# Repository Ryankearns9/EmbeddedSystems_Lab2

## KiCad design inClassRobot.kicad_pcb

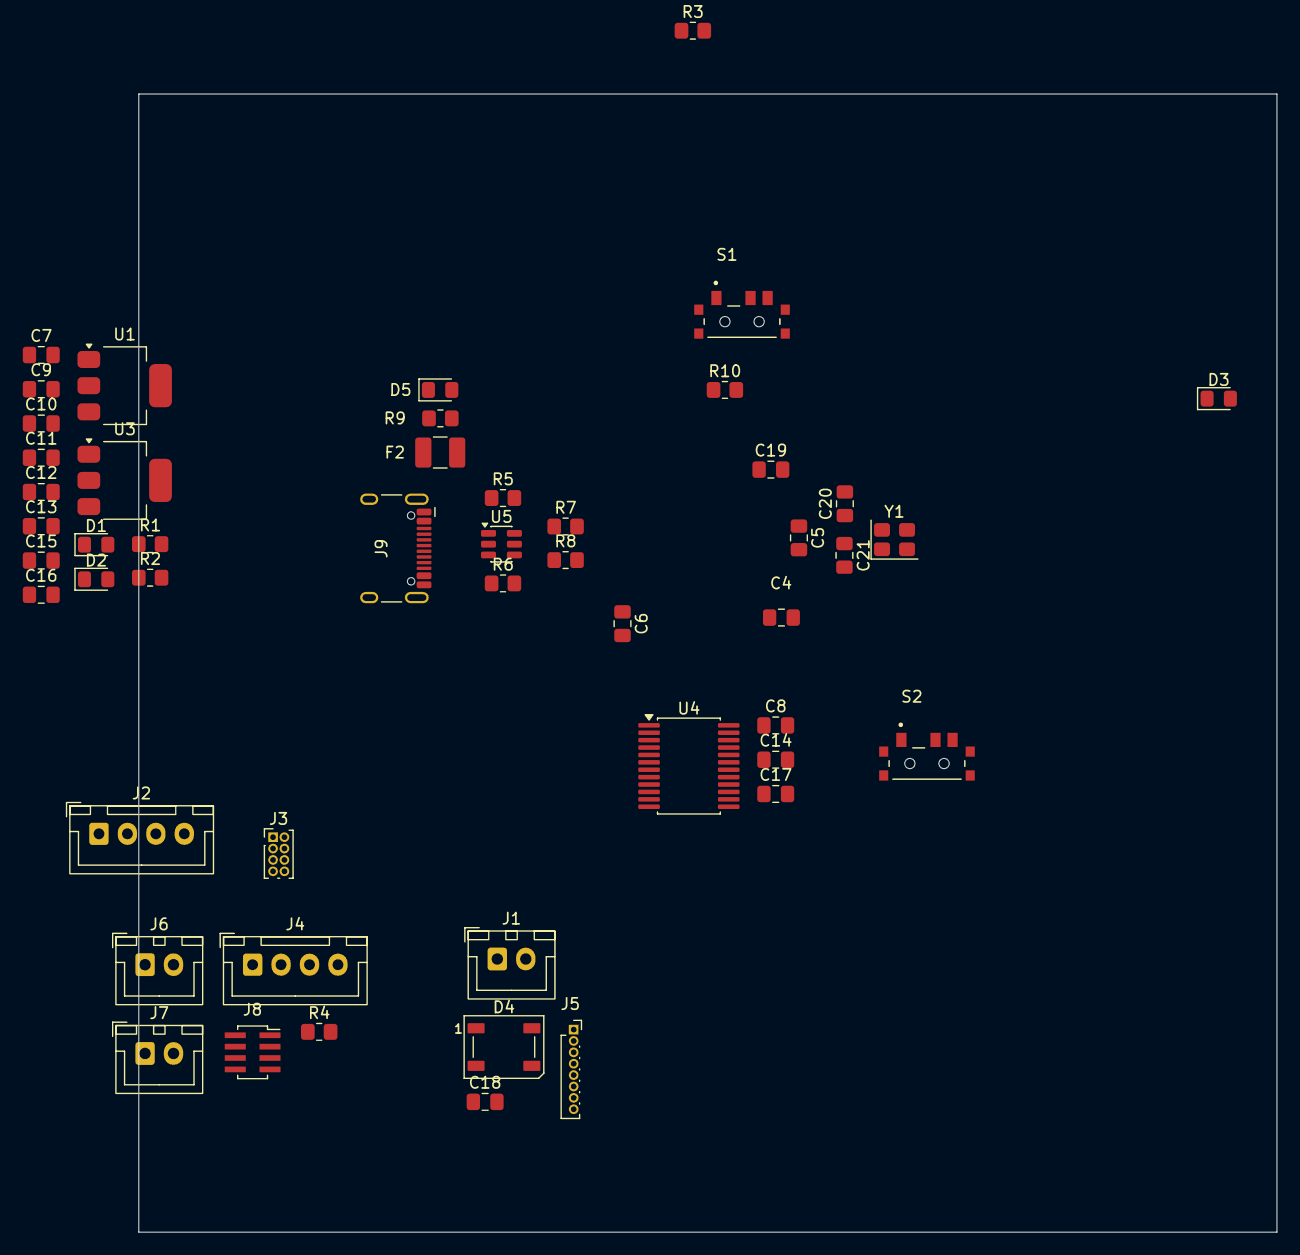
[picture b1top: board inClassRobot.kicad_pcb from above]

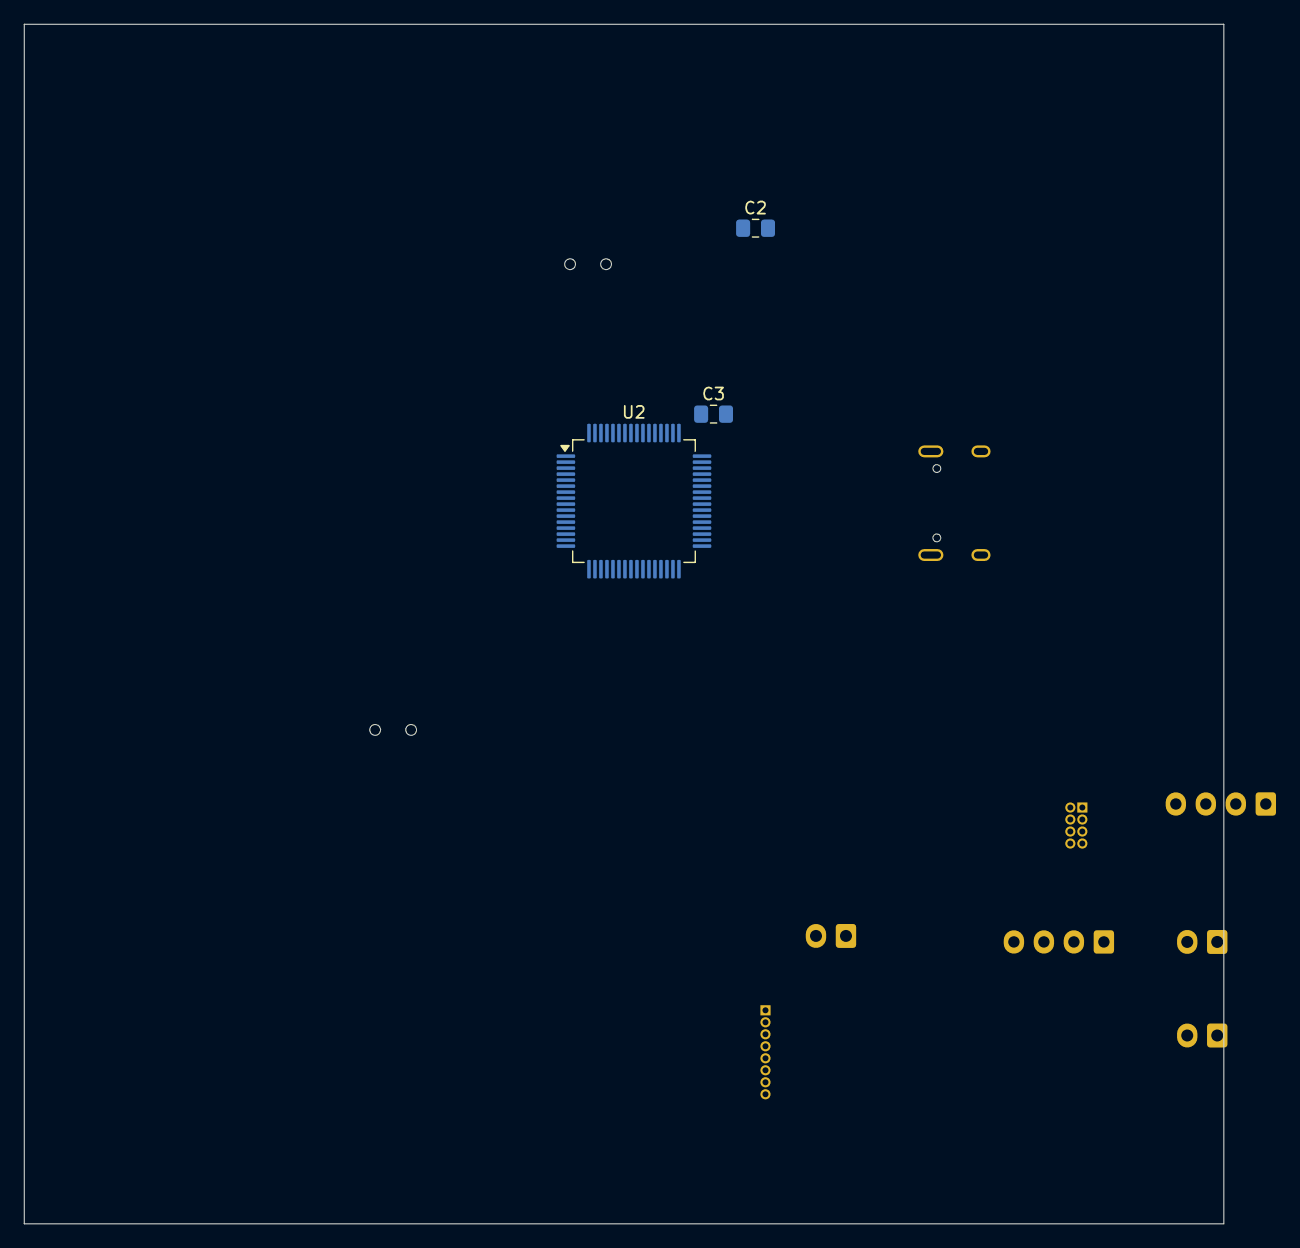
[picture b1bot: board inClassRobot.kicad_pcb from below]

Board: 2 copper layers, 100.0 x 100.0 mm, 53 parts (3 on the bottom side), 48 nets, no tracks yet.

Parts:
C2, C10, C12, C15, C16, C17: 10 uF; C_0805_2012Metric_Pad1.18x1.45mm_HandSolder
C3, C4, C5, C6, C7, C8, C9, C11, C13, C14, C18, C20, C21: 0.1uF; C_0805_2012Metric_Pad1.18x1.45mm_HandSolder
C19: 2.2uF; C_0805_2012Metric_Pad1.18x1.45mm_HandSolder
D1: 3v3_LED; LED_0805_2012Metric_Pad1.15x1.40mm_HandSolder
D2: 5V_LED; LED_0805_2012Metric_Pad1.15x1.40mm_HandSolder
D3: USER_LED; LED_0805_2012Metric_Pad1.15x1.40mm_HandSolder
D4: WS2812B; LED_WS2812B_PLCC4_5.0x5.0mm_P3.2mm
D5: USB_LED; LED_0805_2012Metric_Pad1.15x1.40mm_HandSolder
F2: Polyfuse; Fuse_1210_3225Metric_Pad1.42x2.65mm_HandSolder
J1: BATT_CONN; JST_XH_B2B-XH-A_1x02_P2.50mm_Vertical
J2: ENCODER_CONN; JST_XH_B4B-XH-A_1x04_P2.50mm_Vertical
J3: Conn_01x04; PinHeader_2x04_P1.00mm_Vertical
J4: MT6701_CONN; JST_XH_B4B-XH-A_1x04_P2.50mm_Vertical
J5: CONN_MPU6050; PinSocket_1x08_P1.00mm_Vertical
J6: M1_CONN; JST_XH_B2B-XH-A_1x02_P2.50mm_Vertical
J7: M2_CONN; JST_XH_B2B-XH-A_1x02_P2.50mm_Vertical
J8: ESP_CONN; PinSocket_2x04_P1.00mm_Vertical_SMD
J9: USB_C_Receptacle_USB2.0_14P; USB_C_Receptacle_HCTL_HC-TYPE-C-16P-01A
R1, R2, R3, R9, R10: 1k; R_0805_2012Metric_Pad1.20x1.40mm_HandSolder
R4: 10k; R_0805_2012Metric_Pad1.20x1.40mm_HandSolder
R5, R6, R7, R8: 5.1k; R_0805_2012Metric_Pad1.20x1.40mm_HandSolder
S1, S2: SLW-66527511-SMT-TR; SW_SLW-66527511-SMT-TR
U1, U3: LD1117S50TR_SOT223; SOT-223-3_TabPin2
U2: STM32F401RETx; LQFP-64_10x10mm_P0.5mm
U4: TB6612FNG; SSOP-24_5.3x8.2mm_P0.65mm
U5: USBLC6-2SC6; SOT-23-6
Y1: Crystal_GND24; Crystal_SMD_Abracon_ABM8G-4Pin_3.2x2.5mm

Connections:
5V_REG: C9.1, C10.1, R2.1, U1.2 (VO)
+3.3V: C2.1, C3.1, C4.1, C5.1, C6.1, C8.1, C12.1, C13.1, C14.1, C17.1, J3.1, J8.4, J8.6, J8.8, R1.1, R4.2, S1.1, S2.1, S2.2, S2.3, U2.19 (VDD), U2.32 (VDD), U2.48 (VDD), U2.64 (VDD), U3.2 (VO), U4.13 (VM2), U4.14 (VM3), U4.20 (VCC), U4.24 (VM1)
+5V: C11.1, C16.1, U3.3 (VI)
/ENC_A: J2.2, U2.59 (PB7)
/ENC_B: J2.3, U2.58 (PB6)
/ESD_D+: R8.1, U2.45 (PA12)
/ESD_D-: R7.1, U2.44 (PA11)
/ESP_RX: J8.7, U2.42 (PA9)
/IMU_INT: J5.8, U2.2 (PC13)
/IMU_SCL: J5.3, U2.61 (PB8)
/IMU_SDA: J5.4, U2.62 (PB9)
/MD_A01: J6.1, U4.1 (AO1), U4.2 (AO1)
/MD_A02: J6.2, U4.5 (AO2), U4.6 (AO2)
/MD_AIN1: U2.16 (PA2), U4.21 (AIN1)
/MD_AIN2: U2.17 (PA3), U4.22 (AIN2)
/MD_B01: J7.1, U4.11 (BO1), U4.12 (BO1)
/MD_B02: J7.2, U4.7 (BO2), U4.8 (BO2)
/MD_BIN1: U2.22 (PA6), U4.17 (BIN1)
/MD_BIN2: U2.23 (PA7), U4.16 (BIN2)
/MD_PWMA: U2.15 (PA1), U4.23 (PWMA)
/MD_PWMB: U2.21 (PA5), U4.15 (PWMB)
/MD_STBY: U2.20 (PA4), U4.19 (STBY)
/MT_PMW: J4.3, U2.37 (PC6)
/SWCLK: J3.2, U2.49 (PA14)
/SWDIO: J3.4, U2.46 (PA13)
/USER_LED: R3.1, U2.27 (PB1)
/WS_DIN: D4.4 (DIN), U2.14 (PA0)
ESP_TX: C18.1, D4.1 (VDD), J8.2, U2.43 (PA10)
GND: C2.2, C3.2, C4.2, C5.2, C6.2, C7.2, C8.2, C9.2, C10.2, C11.2, C12.2, C13.2, C14.2, C15.2, C16.2, C17.2, C18.2, C19.2, C20.2, C21.2, D1.1 (K), D2.1 (K), D3.1 (K), D4.3 (VSS), D5.1 (K), J1.2, J2.4, J3.3, J4.2, J5.2, J8.1, J9.A1 (GND), J9.A12 (GND), J9.B1 (GND), J9.B12 (GND), J9.SH (SHIELD), R5.1, R6.1, S1.3, U1.1 (GND), U2.12 (VSSA), U2.18 (VSS), U2.28 (PB2), U2.31 (VSS), U2.47 (VSS), U2.63 (VSS), U3.1 (GND), U4.3 (PGND1), U4.4 (PGND1), U4.9 (PGND2), U4.10 (PGND2), U4.18 (GND), U5.2 (GND), Y1.2 (G), Y1.4 (G)
unnamed: D1.2 (A), R1.2
unnamed: D2.2 (A), R2.2
unnamed: D3.2 (A), R3.2
unnamed: D5.2 (A), R9.1
unnamed: F2.1, J9.A4 (VBUS), J9.A9 (VBUS), J9.B4 (VBUS), J9.B9 (VBUS)
unnamed: J8.5, R4.1
unnamed: J9.A5 (CC1), R5.2
unnamed: J9.B5 (CC2), R6.2
unnamed: J9.A6 (D+), J9.B6 (D+), U5.3 (I/O2)
unnamed: J9.A7 (D-), J9.B7 (D-), U5.1 (I/O1)
unnamed: R7.2, U5.6 (I/O1)
unnamed: R8.2, U5.4 (I/O2)
unnamed: R10.1, S1.2
unnamed: R10.2, U2.60 (BOOT0)
unnamed: C21.1, U2.5 (PH0), Y1.3
unnamed: C20.1, U2.6 (PH1), Y1.1
unnamed: C19.1, U2.30 (VCAP1)
VM: C7.1, C15.1, J1.1, J2.1, J4.1, J5.1, U1.3 (VI)
Vusb: F2.2, R9.2, U5.5 (VBUS)

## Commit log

2026-04-23 Added docs
2026-04-23 Added Board
